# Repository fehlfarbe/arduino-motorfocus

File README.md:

# arduino-motorfocus

Simple moonlite focuser protocol implementation for Arduino and stepper motors.

Tested with Arduino Nano and cheap [28BYJ-48 stepper motor with driver](https://arduino-info.wikispaces.com/SmallSteppers) and [INDI / Ekos](http://indilib.org). Works also with [Pololu A4988 Stepper Motor Driver](https://www.pololu.com/product/1182) (see wiring).

Updated 3D/CAD models for TS 65/420 Quadruplet are available at Thingiverse: <https://www.thingiverse.com/thing:2063325>
Motor focuser for Starlight Feather Touch 2" by Cover1987: <https://www.thingiverse.com/thing:3593910>

## Installation

### Webupload via browser's Web Serial API

Only available for Chrome/Chromium at the moment. Visit <https://fehlfarbe.github.io/arduino-motorfocus>, connect your Arduino Nano and click the right button to upload the latest version :)

### Install via PlatformIO

1. Download and install [PlatformIO](https://platformio.org/install/ide?install=vscode)
2. Clone or download this project and unzip it
3. Open project with PlatformIO
4. Select the right config for your microcontroller e.g. `nanoatmega328` for Arduino Nano with 28BYJ-48 stepper, `promicro16` for Sparkfun Pro Mirco with 28BYJ-48 stepper or `nanoatmega328_A988driver` for Arduino Nano with A4988driver support in the bottom bar and upload to your Arduino (PlatformIO will download needed libraries automatically)

## Wiring

### Wiring for 28BYJ-48 stepper motor with ULN2003A breakout board

### Wiring for A4988 driver

Select config `A4988driver` in VSCode bottom bar (step 4). You can change the microstep resolution (full step, half step, ...) with MS1, MS2, MS3 pins on the driver board. See more at [Pololu A4988 Stepper Motor Driver doc](https://www.pololu.com/product/1182) (Step (and microstep) size). If all pins are unconnected the driver will run in full step mode.

### Wiring for in/out buttons

The internal pullups are active so you have to connect your buttons for manual focus to GND. The potentiometer is optional and can limit the maximum speed for manual focus. You can use a linear 100k poti.

### Wiring for temperature sensor DS18B20

You need a 4.7kΩ pullup resistor. If there is no sensor attached the temperatur will be zero.

## Troubleshooting

### ASCOM driver cant find the focuser

Some people reported problems with arduino-motorfocus and Windows/ASCOM. If you use the ASCOM-Moonlite.DRO.Focuser driver the focuser doesn't appear in the setup list.

This happens because the setup opens all COM ports, sends a command and waits for a proper response. Unfortunally Windows resets the device when the port is opened (DTR is set to low) and an Arduino clone needs a second or so to boot up so it won't receive the command and the setup gets a timeout. There are multiple ways to solve the problem:

1. You can flash the [MiniCore Bootloader](https://github.com/MCUdude/MiniCore) to your Arduino. This bootloader is faster and in my tests it was fast enough to get detected by the setup

2. Just install a 10µF or 33µF between RST and GND or remove the 100nF capacitor on the bottom of your Nano. You can see an image of the capacitor and further explanation on [this website](https://www.astroscopic.com/blog/disable-arduinos-auto-reset-connection)

3. Use a different Microcontroller like Arduino Pro Mini with an external USB-TTL converter and dont't connect the DTR line

And voilà the focuser will show up:

### ASCOM driver finds the focuser but can't connect

Same problem as above. Unfortunally the first solution, flashing the bootloader, didn't work for me but the additional capacitor between RST and GND works.

### Other ASCOM errors

If there are different errors, please [open an issue](https://github.com/fehlfarbe/arduino-motorfocus/issues) and attach the logfile. You can activate logging for you focuser in the properties setup:

The logfile is located in `%HOMEPATH%\Documents\ASCOM`

You can also connect an USB-TTL converter to GPIO 10 to see all commands sent by your computer and some debug messages.

### The motor moves very slow

* Don't use a DEBUG build because SoftwareSerial printing slows down the microcontroller
* Check the full/half/... microstep setup of your driver
* Increase SPEED_MULTIPLICATOR and ACCELERATION in arduino-motorfocus.h

### The motor doesn't move

* Check wiring between microcontroller and your driver
* Check if manual focusing via buttons is working
* Check wiring between motor and driver, sometimes the motor coil cables are mixed up

## PCB

I made a simple PCB that connects all the parts and supports Pololu style driver boards and ULN2003A breakout board. The KiCAD project and gerber files are located at `hardware`.

## Arduino-motorfocus mounted on TS65/420 Quadruplet

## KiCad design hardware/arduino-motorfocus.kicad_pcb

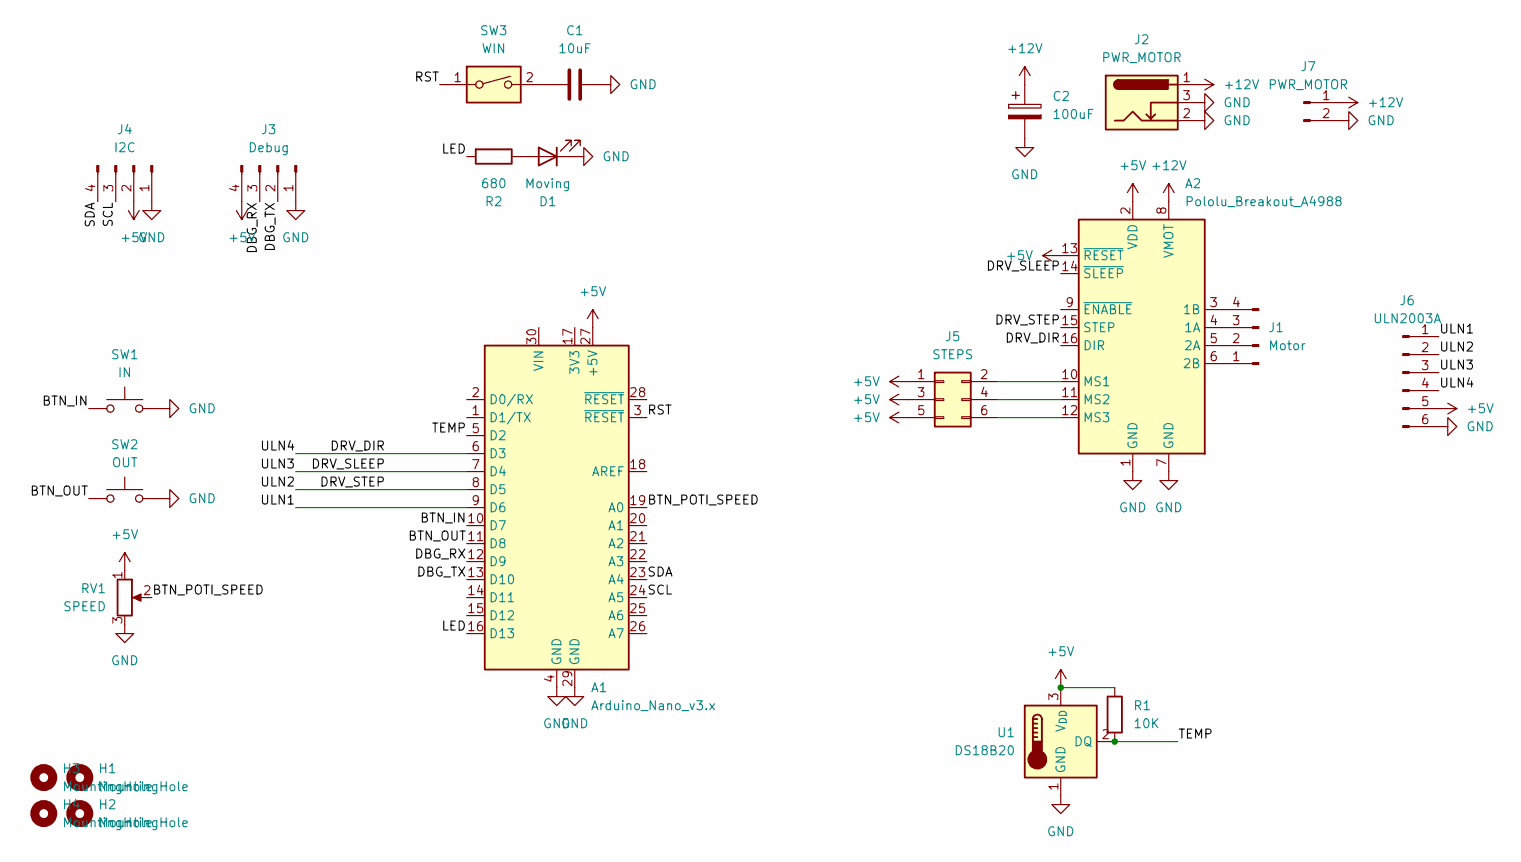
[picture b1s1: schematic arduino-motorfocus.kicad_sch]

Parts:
A1: Arduino_Nano_v3.x; Arduino_Nano
A2: Pololu_Breakout_A4988; Pololu_Breakout-16_15.2x20.3mm
C1: 10uF; C_1206_3216Metric
C2: 100uF; CP_Elec_6.3x5.9
D1: Moving; LED_0805_2012Metric
H1, H2, H3, H4: MountingHole; MountingHole_3.2mm_M3
J1: Motor; JST_XH_B4B-XH-A_1x04_P2.50mm_Vertical
J2: PWR_MOTOR; BarrelJack_Horizontal
J3: Debug; PinHeader_1x04_P2.54mm_Vertical
J4: I2C; PinHeader_1x04_P2.54mm_Vertical
J5: STEPS; PinHeader_2x03_P2.54mm_Vertical
J6: ULN2003A; PinHeader_1x06_P2.54mm_Vertical
J7: PWR_MOTOR; PinHeader_1x02_P2.54mm_Vertical
R1: 10K; R_1206_3216Metric
R2: 680; R_1206_3216Metric
RV1: SPEED; Potentiometer_Vishay_T73YP_Vertical
SW1: IN; SW_SPST_CK_RS282G05A3
SW2: OUT; SW_SPST_CK_RS282G05A3
SW3: WIN; SW_DIP_SPSTx01_Slide_6.7x4.1mm_W6.73mm_P2.54mm_LowProfile_J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
U1: DS18B20; TO-92_Inline

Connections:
+5V: A1.27 (+5V), A2.2 (VDD), A2.13 (~RESET), J3.4, J4.2, J5.1, J5.3, J5.5, J6.5, R1.1, RV1.1, U1.3 (V_{DD})
+12V: A2.8 (VMOT), C2.1, J2.1, J7.1
/BTN_IN: A1.10 (D7), SW1.1
/BTN_OUT: A1.11 (D8), SW2.1
/BTN_POTI_SPEED: A1.19 (A0), RV1.2
/DBG_RX: A1.12 (D9), J3.3
/DBG_TX: A1.13 (D10), J3.2
/DRV_DIR: A1.6 (D3), A2.16 (DIR), J6.4
/DRV_SLEEP: A1.7 (D4), A2.14 (~SLEEP), J6.3
/DRV_STEP: A1.8 (D5), A2.15 (STEP), J6.2
/LED: A1.16 (D13), R2.2
/RST: A1.3 (~RESET), SW3.1
/SCL: A1.24 (A5), J4.3
/SDA: A1.23 (A4), J4.4
/TEMP: A1.5 (D2), R1.2, U1.2 (DQ)
/ULN1: A1.9 (D6), J6.1
GND: A1.4 (GND), A1.29 (GND), A2.1 (GND), A2.7 (GND), C1.2, C2.2, D1.1 (K), J2.2, J2.3, J3.1, J4.1, J6.6, J7.2, RV1.3, SW1.2, SW2.2, U1.1 (GND)
unnamed: A2.4 (1A), J1.3
unnamed: A2.3 (1B), J1.4
unnamed: A2.5 (2A), J1.2
unnamed: A2.6 (2B), J1.1
unnamed: A2.10 (MS1), J5.2
unnamed: A2.11 (MS2), J5.4
unnamed: A2.12 (MS3), J5.6
unnamed: C1.1, SW3.2
unnamed: D1.2 (A), R2.1

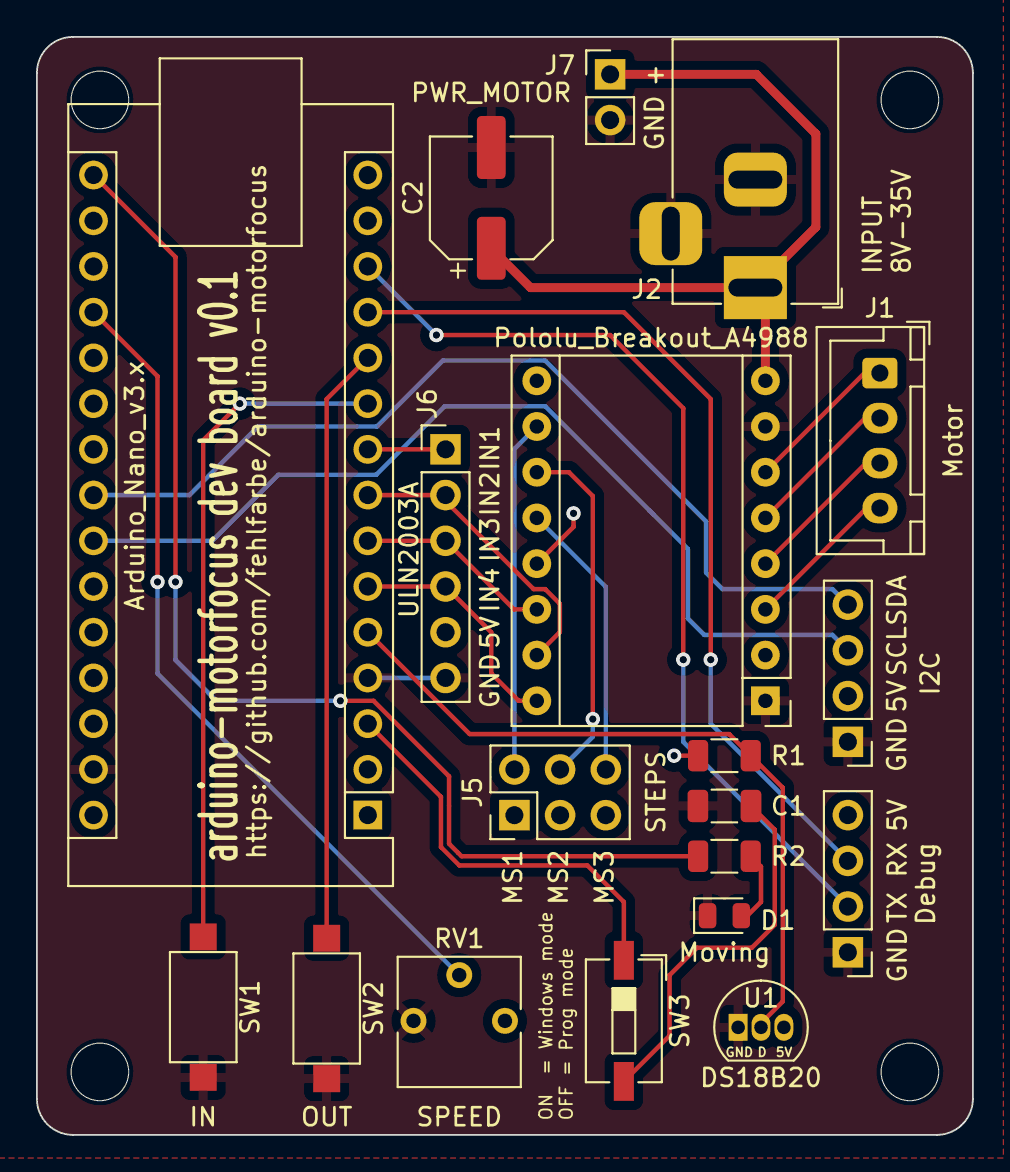
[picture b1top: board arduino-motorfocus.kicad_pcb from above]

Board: 2 copper layers, 52.0 x 61.0 mm, 23 parts (0 on the bottom side), 26 nets.

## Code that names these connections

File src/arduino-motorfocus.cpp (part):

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#include <TimerOne.h>
#include "DummySerial.h"

#define BTN_IN 7
#define BTN_OUT 8
#define BTN_POTI_SPEED A0
#define BTN_MIN_SPEED 8
#define BTN_MAX_SPEED 512
#define BTN_ACCEL_FACTOR 1.05f
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  }

  // setup buttons
  pinMode(BTN_IN, INPUT_PULLUP);
  pinMode(BTN_OUT, INPUT_PULLUP);
  pinMode(BTN_POTI_SPEED, INPUT_PULLUP);

  // init timer
  Timer1.initialize(PERIOD_US);
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
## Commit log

2017-10-02 move serial debugging to non conflicting pins
2017-10-02 disable motor pins when idle
2017-10-02 update currentPosition after stopping to correctly trigger the idle state
2018-02-23 Added input pins to control focus via button Added CMake project structure (for CLion)
2018-08-29 Added Thingiverse link to models
2019-02-12 Added wiring Updated README.md
2019-02-17 Added support for Pololu A4988 driver Changed debug serial interface pins Added input pullups Added some wiring Increased acceleration
2019-04-28 Set driver to default updated README
2019-04-28 revert changes, make 28BYJ-48 with driver board default again
2019-05-25 Added temperature sensor support
2020-09-07 Removed CMake stuff
2020-12-16 Small bugfixes and updated README
2020-12-17 Bugfix so it doesn't close connection to DualFocuser App
2021-01-03 Use of timer interrupt for the stepper.run call
    With the stepper.run() call in the arduino loop(), the motor stalls on heavy serial activity. Using a timer driven interrupt avoids that.
2021-03-17 Added Dummy Debug to prevent motor stuttering
2021-10-10 - Converted Arduino project to PlatformIO project - Minor improvements (code, doc, etc.)
2021-12-01 fixed iss9 DS18B20 wrong wiring
2021-12-01 fixes #9 DS18B20 wrong wiring
2021-12-07 fixes #10 and changed lastSavedPosition to same data type as currentPosition
2021-12-07 Added support for Sparfun Pro Micro tested with indi and manual switches only
2021-12-07 making branch to enable pull request
2021-12-08 Created several configs for Arduino Nano and Sparkfun Pro Micro (#11)
2022-08-22 Fixes #17
2022-10-30 Create LICENSE
2023-01-02 Fixes #18
2023-02-06 Added Arduino Nano with new bootloader to platformio.ini (issue #19)
2023-02-27 Fixed wrong "moving motor" response after button press and some code improvements
2023-08-02 Updated RST capacitor size to a higher value
2023-08-03 Added support for poti that controls the motor speed on button press
2023-08-03 Inverted poti signal so if there is nothing connected the motor will still run and minimum speed
2023-08-05 Using timer and acceleration in button/manual mode
2023-08-06 Better acceleration in maual mode
2023-08-07 Added build and CI scripts
2023-08-07 Fixed CI build scripts
2023-08-29 Fixing motor running state
2023-08-31 Created simple dev board that supports ULN2003A and A4988 driver board
2023-09-23 Added simple PCB project and doc
2023-09-23 Improved README (issue #25)
2023-09-23 Init webupload for github pages
2023-10-01 Added very simple webupload page
2023-10-01 moved webupload to docs
2023-10-01 Releases have to be at a relative path
2023-10-01 Updated webupload to v1.0.2
2024-01-20 Added first try for Arduino Uno with CNC shield (issue #27)
2024-01-20 Changed pins for one wire bus and btn out
2024-01-23 Changed pin config for cnc shield (issue #27)
2024-01-24 Fixing no negatives values for temperature sensor (issue #28)
2025-01-22 Implemented BLE support for ESP32-C3 (issue #31)
2025-12-21 Added potentiometer value to doc
2025-12-21 Added some additional doc to code and fix #33
